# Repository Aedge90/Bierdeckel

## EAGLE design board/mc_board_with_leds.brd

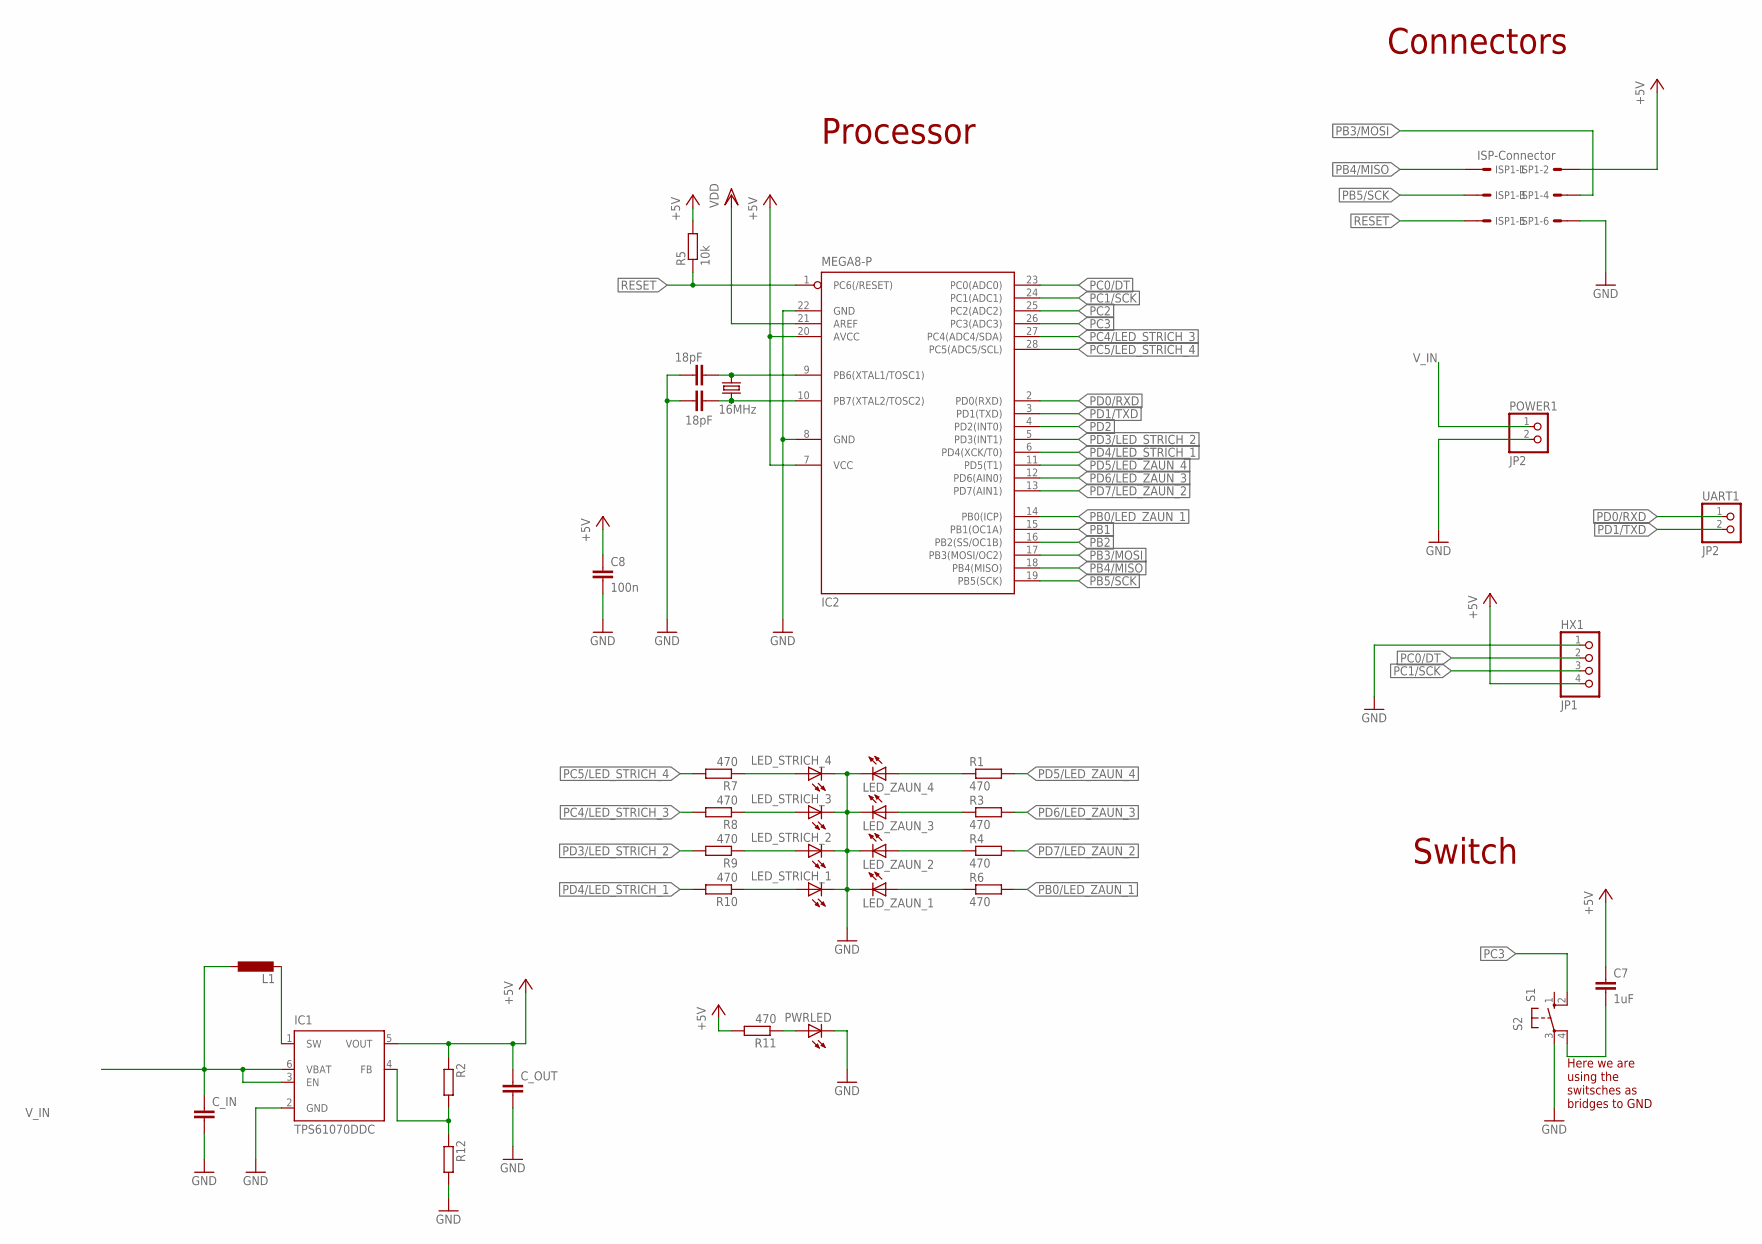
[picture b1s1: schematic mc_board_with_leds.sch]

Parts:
C5, C6: 18pF; C0805K
C7: 1uF; C0805
C8: 100n; C0805
C_IN: C-EUC0805; C0805
C_OUT: C-EUC0805; C0805
HX1: JP1; 1X04
IC1: TPS61070DDC; TSOT23-6_DDC
IC2: MEGA8-P; DIL28-3
ISP1: ISP-Connector; 057-006-1
L1: L-EUL4532P; L4532P
LED_STRICH_1, LED_STRICH_2, LED_STRICH_3, LED_STRICH_4: LED3MM
LED_ZAUN_1, LED_ZAUN_2, LED_ZAUN_3, LED_ZAUN_4: LED3MM
POWER1: JP2; 1X02
PWRLED: LED3MM
Q2: 16MHz; HC49/S
R1, R3, R4, R6, R7, R8, R9, R10, R11: 470; R0805
R2, R12: R-EU_R0805; R0805
R5: 10k; R1206
S2: S1; B3F-10XX
UART1: JP2; 1X02

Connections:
+5V: C7.1, C8.1, C_OUT.1, HX1.4, IC1.5 (VOUT), IC2.7 (VCC), IC2.20 (AVCC), ISP1.2, R2.1, R5.2, R11.2; also elsewhere on the board
GND: C5.2, C6.2, C8.2, C_IN.2, C_OUT.2, HX1.1, IC1.2 (GND), IC2.8 (GND), IC2.22 (GND), ISP1.6, LED_STRICH_1.K (C), LED_STRICH_2.K (C), LED_STRICH_3.K (C), LED_STRICH_4.K (C), LED_ZAUN_1.K (C), LED_ZAUN_2.K (C), LED_ZAUN_3.K (C), LED_ZAUN_4.K (C), POWER1.2, PWRLED.K (C), R12.2, S2.3; also elsewhere on the board
unnamed: LED_ZAUN_4.A, R1.1
unnamed: LED_ZAUN_3.A, R3.1
unnamed: LED_ZAUN_2.A, R4.1
unnamed: C5.1, IC2.10 (PB7(XTAL2/TOSC2)), Q2.2
unnamed 6: IC1.1 (SW), L1.2; also elsewhere on the board
unnamed: LED_ZAUN_1.A, R6.1
unnamed: LED_STRICH_4.A, R7.1
unnamed: LED_STRICH_3.A, R8.1
unnamed: LED_STRICH_2.A, R9.1
unnamed: LED_STRICH_1.A, R10.1
unnamed: PWRLED.A, R11.1
unnamed: C6.1, IC2.9 (PB6(XTAL1/TOSC1)), Q2.1
unnamed: C7.2, S2.4 (P1)
unnamed: IC1.4 (FB), R2.2, R12.1
PB0/LED_ZAUN_1: IC2.14 (PB0(ICP)), R6.2
PB1: IC2.15 (PB1(OC1A))
PB2: IC2.16 (PB2(SS/OC1B))
PB3/MOSI: IC2.17 (PB3(MOSI/OC2)), ISP1.4
PB4/MISO: IC2.18 (PB4(MISO)), ISP1.1
PB5/SCK: IC2.19 (PB5(SCK)), ISP1.3
PC0/DT: HX1.2, IC2.23 (PC0(ADC0))
PC1/SCK: HX1.3, IC2.24 (PC1(ADC1))
PC2: IC2.25 (PC2(ADC2))
PC3: IC2.26 (PC3(ADC3)), S2.2 (S1)
PC4/LED_STRICH_3: IC2.27 (PC4(ADC4/SDA)), R8.2
PC5/LED_STRICH_4: IC2.28 (PC5(ADC5/SCL)), R7.2
PD0/RXD: IC2.2 (PD0(RXD)), UART1.1
PD1/TXD: IC2.3 (PD1(TXD)), UART1.2
PD2: IC2.4 (PD2(INT0))
PD3/LED_STRICH_2: IC2.5 (PD3(INT1)), R9.2
PD4/LED_STRICH_1: IC2.6 (PD4(XCK/T0)), R10.2
PD5/LED_ZAUN_4: IC2.11 (PD5(T1)), R1.2
PD6/LED_ZAUN_3: IC2.12 (PD6(AIN0)), R3.2
PD7/LED_ZAUN_2: IC2.13 (PD7(AIN1)), R4.2
RESET: IC2.1 (PC6(/RESET)), ISP1.5, R5.1
VDD: IC2.21 (AREF)
V_IN: C_IN.1, IC1.3 (EN), IC1.6 (VBAT), L1.1, POWER1.1; also elsewhere on the board

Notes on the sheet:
Connectors
Switch
Processor
Here we are using the switsches as bridges to GND

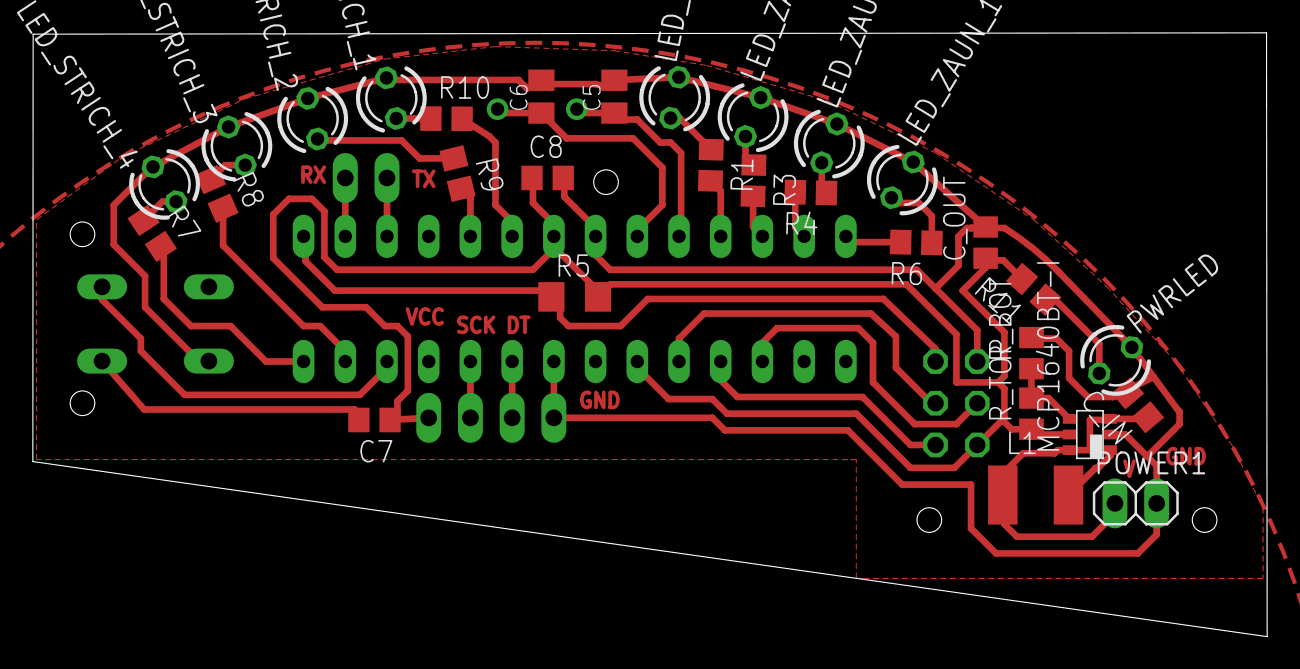
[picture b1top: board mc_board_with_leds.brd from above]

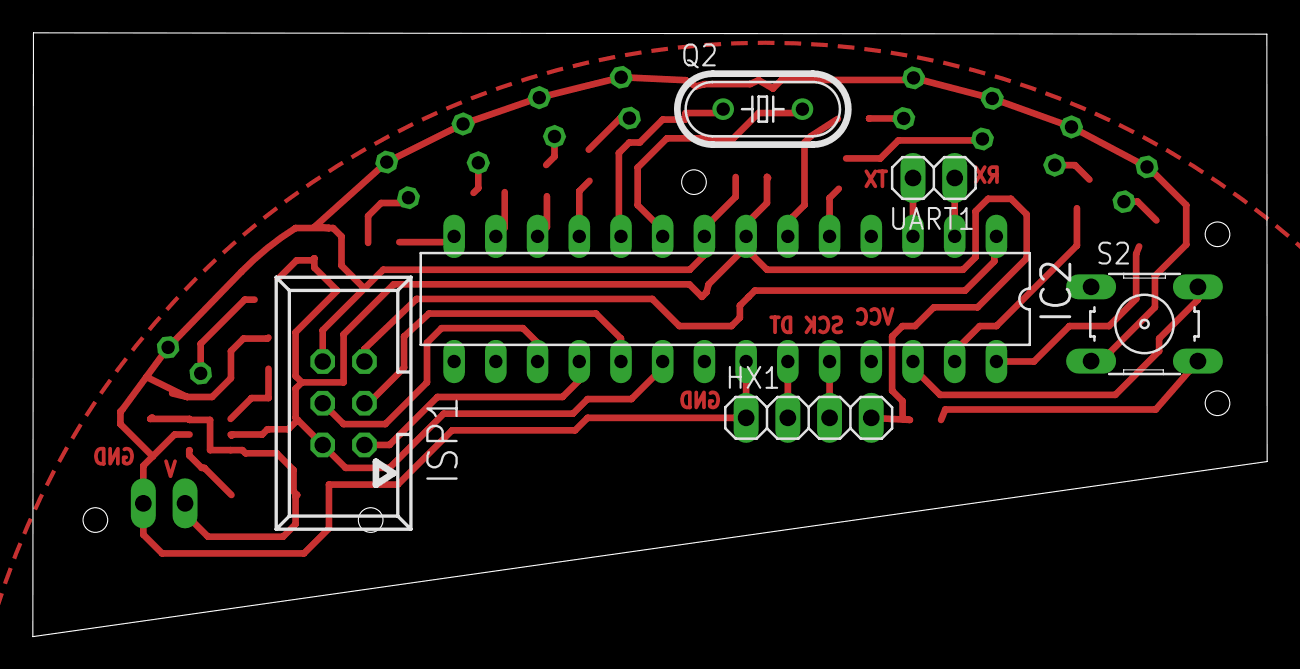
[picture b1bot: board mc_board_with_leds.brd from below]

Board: 2 copper layers, 75.2 x 36.8 mm, 36 parts (6 on the bottom side), 34 nets.

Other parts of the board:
MCP1640BT-I: TPS61070DDC; TSOT23-6_DDC
R_BOT: 330k; R0805
R_TOP: 560k; R0805

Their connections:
+5V: MCP1640BT-I.5, R_TOP.1; also elsewhere on the board
GND: MCP1640BT-I.2, R_BOT.2; also elsewhere on the board
unnamed 6: MCP1640BT-I.1; also elsewhere on the board
unnamed: MCP1640BT-I.4, R_BOT.1, R_TOP.2
V_IN: MCP1640BT-I.3, MCP1640BT-I.6; also elsewhere on the board

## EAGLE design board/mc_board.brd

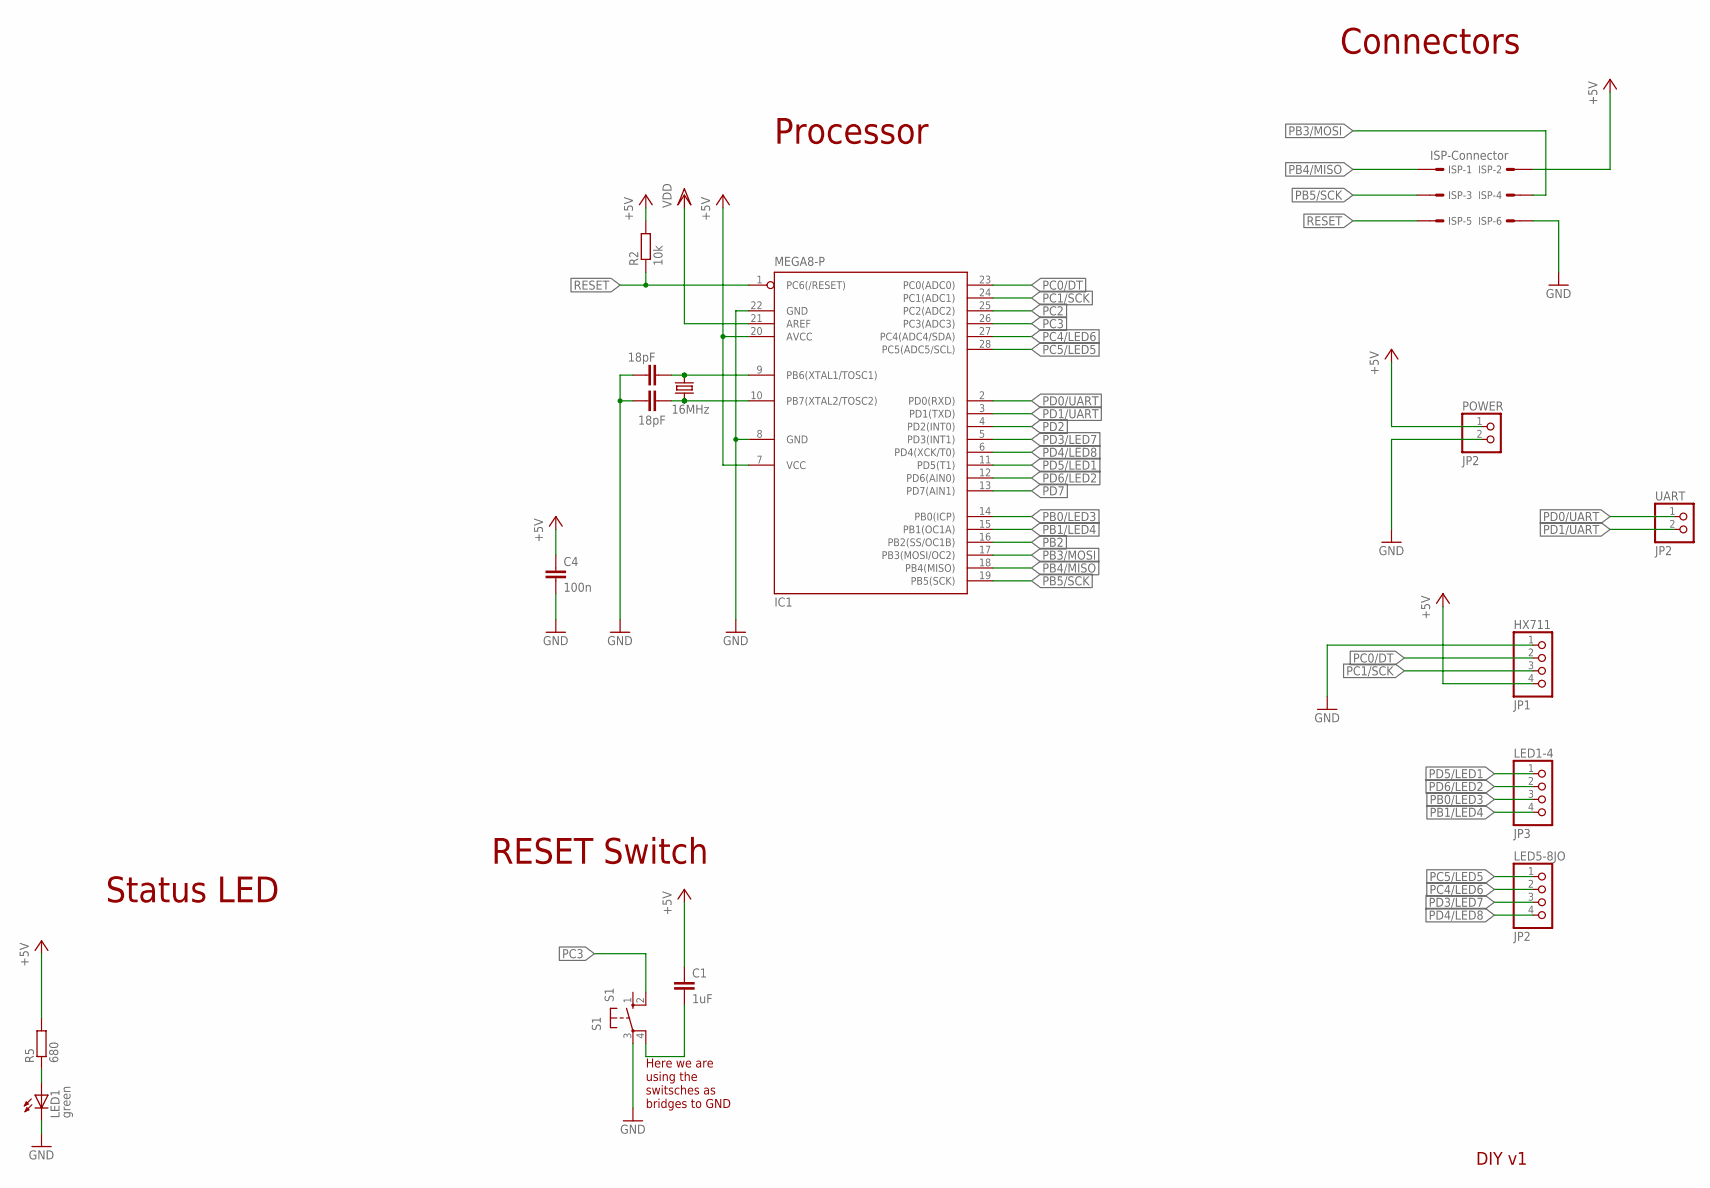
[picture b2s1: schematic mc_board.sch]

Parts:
C1: 1uF; C0805
C2, C3: 18pF; C0805K
C4: 100n; C0805
HX711: JP1; 1X04
IC1: MEGA8-P; DIL28-3
ISP: ISP-Connector; 057-006-1
LED1: green; CHIPLED_0805
LED1-4: JP3; 1X04
LED5-8JO: JP2; 1X04
POWER: JP2; 1X02
Q1: 16MHz; HC49/S
R2: 10k; R1206
R5: 680; R0805
S1: S1; B3F-10XX
UART: JP2; 1X02

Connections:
+5V: C1.1, C4.1, HX711.4, IC1.7 (VCC), IC1.20 (AVCC), ISP.2, POWER.1, R2.2, R5.2
GND: C2.2, C3.2, C4.2, HX711.1, IC1.8 (GND), IC1.22 (GND), ISP.6, LED1.C, POWER.2, S1.3
unnamed: LED1.A, R5.1
unnamed: C3.1, IC1.9 (PB6(XTAL1/TOSC1)), Q1.1
unnamed: C2.1, IC1.10 (PB7(XTAL2/TOSC2)), Q1.2
unnamed: C1.2, S1.4 (P1)
PB0/LED3: IC1.14 (PB0(ICP)), LED1-4.3
PB1/LED4: IC1.15 (PB1(OC1A)), LED1-4.4
PB2: IC1.16 (PB2(SS/OC1B))
PB3/MOSI: IC1.17 (PB3(MOSI/OC2)), ISP.4
PB4/MISO: IC1.18 (PB4(MISO)), ISP.1
PB5/SCK: IC1.19 (PB5(SCK)), ISP.3
PC0/DT: HX711.2, IC1.23 (PC0(ADC0))
PC1/SCK: HX711.3, IC1.24 (PC1(ADC1))
PC2: IC1.25 (PC2(ADC2))
PC3: IC1.26 (PC3(ADC3)), S1.2 (S1)
PC4/LED6: IC1.27 (PC4(ADC4/SDA)), LED5-8JO.2
PC5/LED5: IC1.28 (PC5(ADC5/SCL)), LED5-8JO.1
PD0/UART: IC1.2 (PD0(RXD)), UART.1
PD1/UART: IC1.3 (PD1(TXD)), UART.2
PD2: IC1.4 (PD2(INT0))
PD3/LED7: IC1.5 (PD3(INT1)), LED5-8JO.3
PD4/LED8: IC1.6 (PD4(XCK/T0)), LED5-8JO.4
PD5/LED1: IC1.11 (PD5(T1)), LED1-4.1
PD6/LED2: IC1.12 (PD6(AIN0)), LED1-4.2
PD7: IC1.13 (PD7(AIN1))
RESET: IC1.1 (PC6(/RESET)), ISP.5, R2.1
VDD: IC1.21 (AREF)

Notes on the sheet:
Status LED
Connectors
RESET Switch
DIY v1
Processor
Here we are using the switsches as bridges to GND

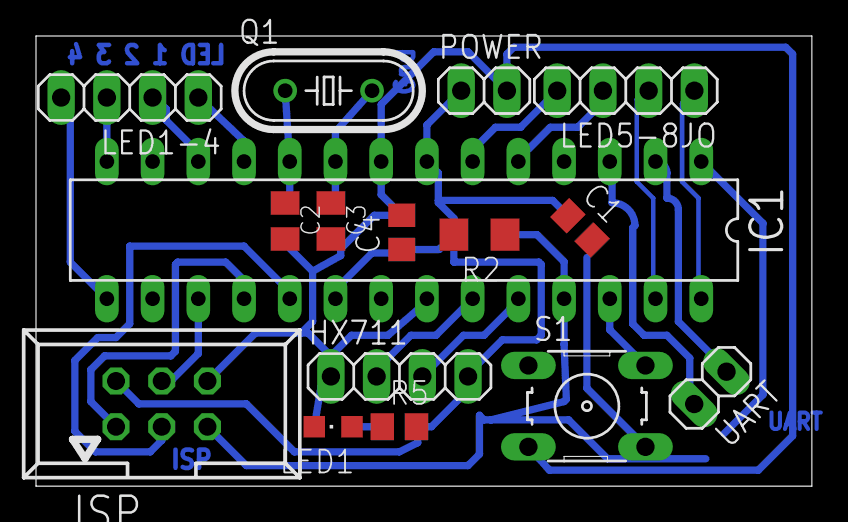
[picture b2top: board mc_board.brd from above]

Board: 2 copper layers, 43.1 x 25.0 mm, 16 parts (0 on the bottom side), 23 nets.

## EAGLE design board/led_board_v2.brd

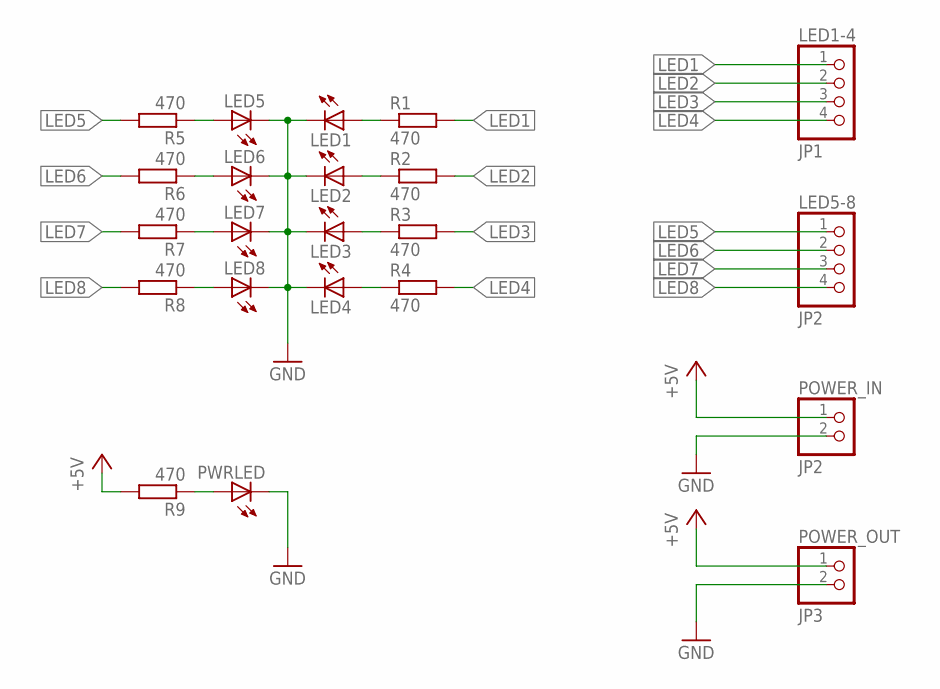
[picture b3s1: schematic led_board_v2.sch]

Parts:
LED1, LED2, LED3, LED4, LED5, LED6, LED7, LED8: LED3MM
LED1-4: JP1; 1X04
LED5-8: JP2; 1X04
POWER_IN: JP2; 1X02
POWER_OUT: JP3; 1X02
PWRLED: LED3MM
R1, R2, R3, R4, R5, R6, R7, R8, R9: 470; R0805

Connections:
+5V: POWER_IN.1, POWER_OUT.1, R9.2
GND: LED1.K (C), LED2.K (C), LED3.K (C), LED4.K (C), LED5.K (C), LED6.K (C), LED7.K (C), LED8.K (C), POWER_IN.2, POWER_OUT.2, PWRLED.K (C)
LED1: LED1-4.1, R1.2
LED2: LED1-4.2, R2.2
LED3: LED1-4.3, R3.2
LED4: LED1-4.4, R4.2
LED5: LED5-8.1, R5.2
LED6: LED5-8.2, R6.2
LED7: LED5-8.3, R7.2
LED8: LED5-8.4, R8.2
unnamed: LED1.A, R1.1
unnamed: LED2.A, R2.1
unnamed: LED3.A, R3.1
unnamed: LED4.A, R4.1
unnamed: LED5.A, R5.1
unnamed: LED6.A, R6.1
unnamed: LED7.A, R7.1
unnamed: LED8.A, R8.1
unnamed: PWRLED.A, R9.1

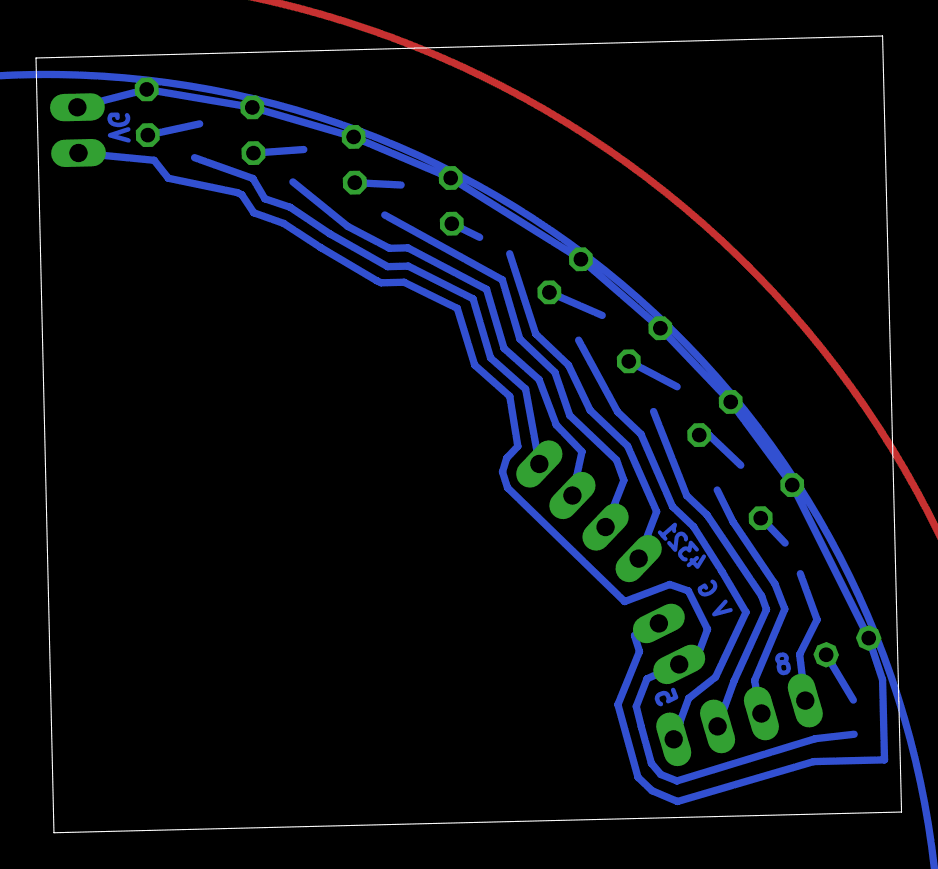
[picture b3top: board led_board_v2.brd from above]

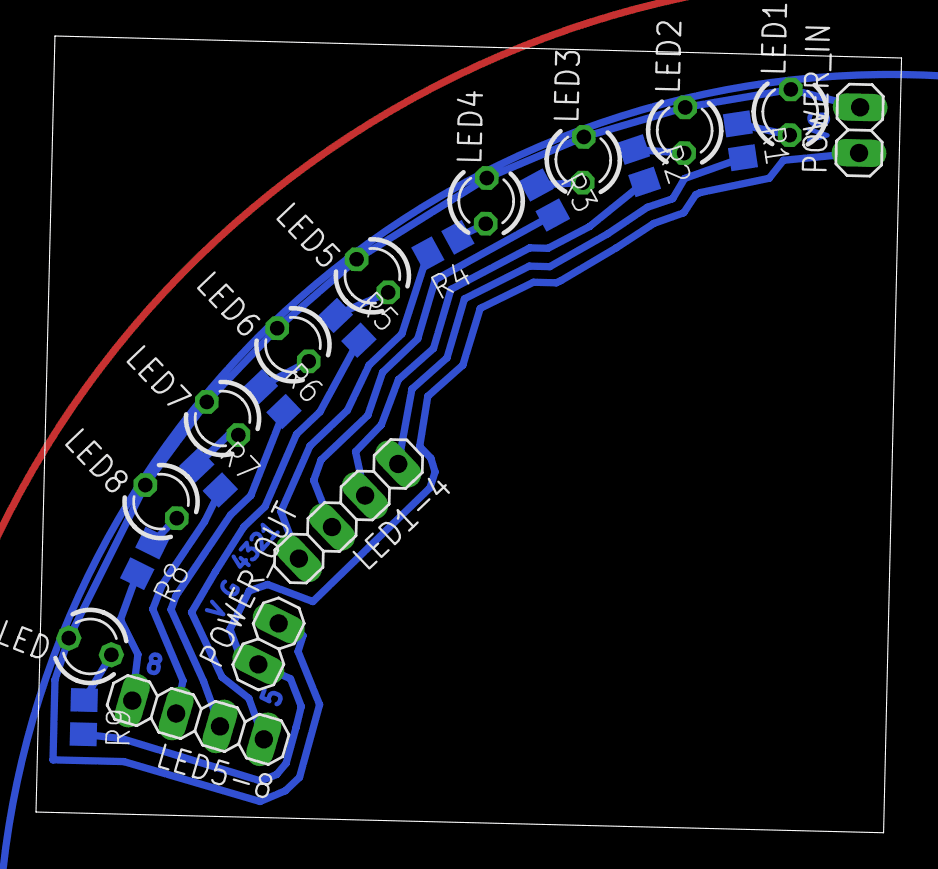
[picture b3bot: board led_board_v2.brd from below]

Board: 2 copper layers, 48.1 x 44.3 mm, 22 parts (22 on the bottom side), 19 nets.

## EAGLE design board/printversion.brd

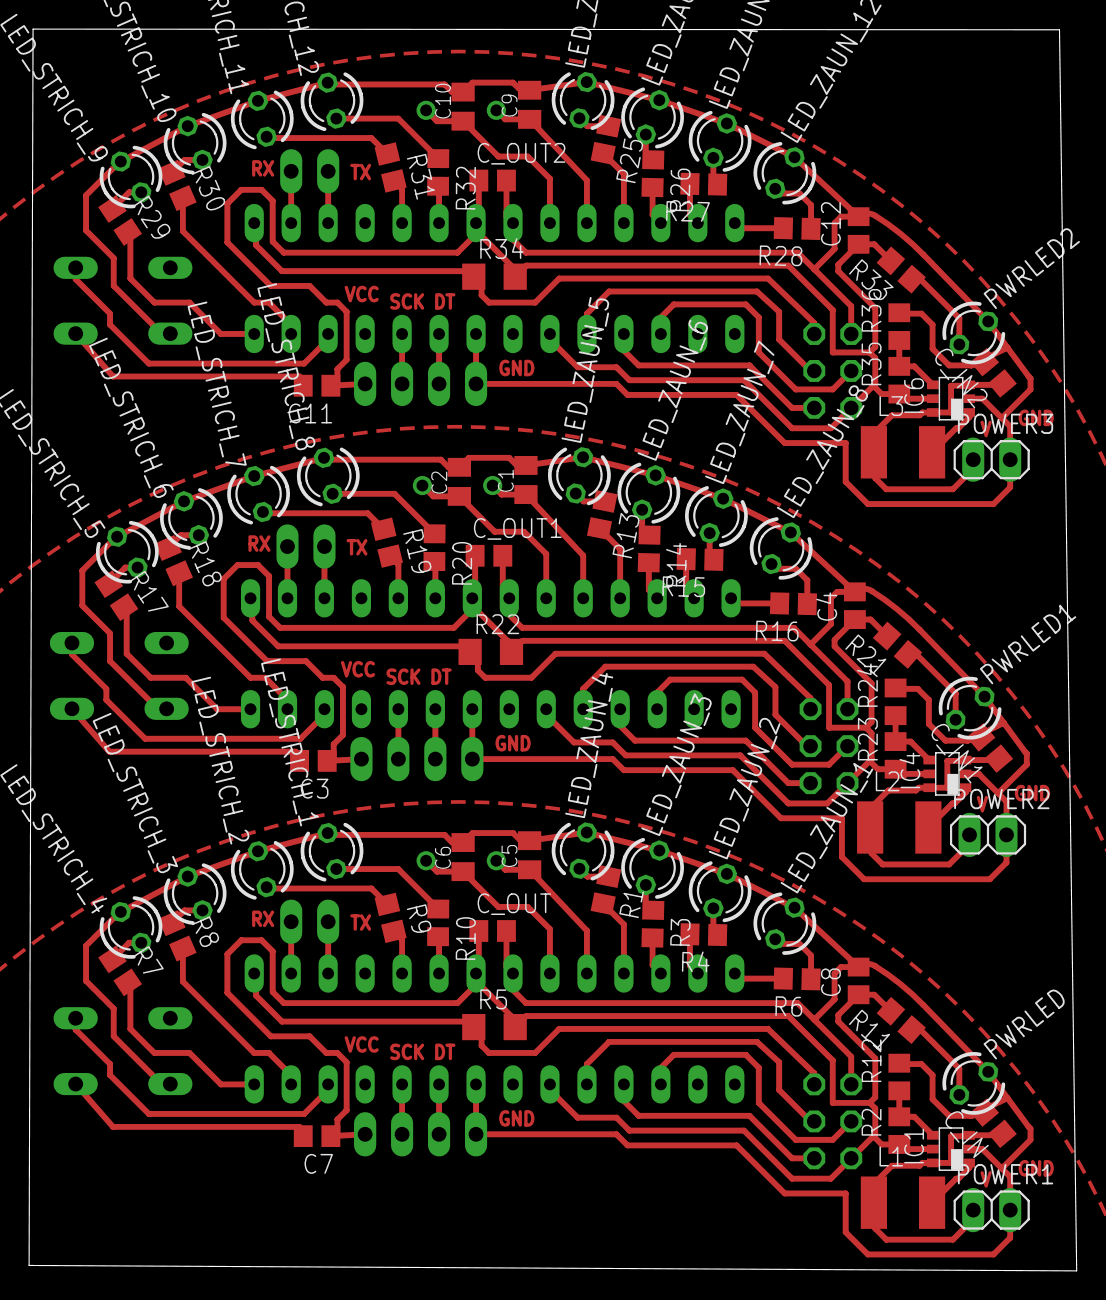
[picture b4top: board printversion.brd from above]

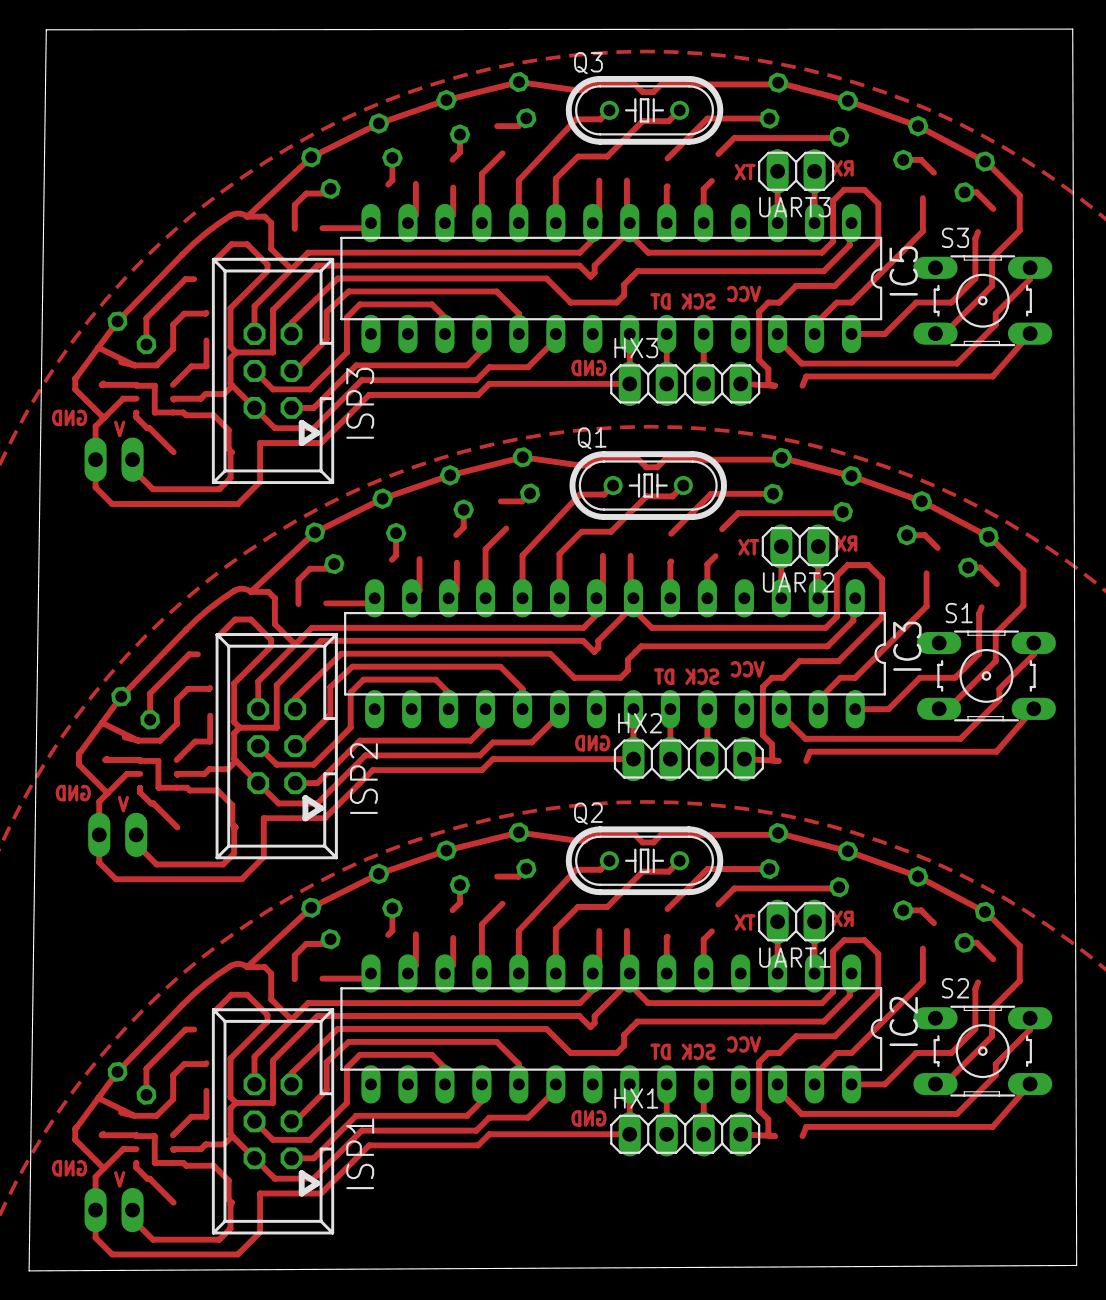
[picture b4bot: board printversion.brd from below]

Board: 2 copper layers, 72.0 x 85.3 mm, 108 parts (18 on the bottom side), 102 nets.

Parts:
C1, C2, C5, C6, C9, C10: 18pF; C0805K
C3, C7, C11: 1uF; C0805
C4, C8, C12: 100n; C0805
C_IN, C_IN1, C_IN2: C0805
C_OUT, C_OUT1, C_OUT2: C0805
HX1, HX2, HX3: JP1; 1X04
IC1, IC4, IC6: TPS61070DDC; TSOT23-6_DDC
IC2, IC3, IC5: MEGA8-P; DIL28-3
ISP1, ISP2, ISP3: ISP-Connector; 057-006-1
L1, L2, L3: L4532P
LED_STRICH_1, LED_STRICH_2, LED_STRICH_3, LED_STRICH_4, LED_STRICH_5, LED_STRICH_6, LED_STRICH_7, LED_STRICH_8, LED_STRICH_9, LED_STRICH_10, LED_STRICH_11, LED_STRICH_12: LED3MM
LED_ZAUN_1, LED_ZAUN_2, LED_ZAUN_3, LED_ZAUN_4, LED_ZAUN_5, LED_ZAUN_6, LED_ZAUN_7, LED_ZAUN_8, LED_ZAUN_9, LED_ZAUN_10, LED_ZAUN_11, LED_ZAUN_12: LED3MM
POWER1, POWER2, POWER3: JP2; 1X02
PWRLED, PWRLED1, PWRLED2: LED3MM
Q1, Q2, Q3: 16MHz; HC49/S
R1, R3, R4, R6, R7, R8, R9, R10, R11, R13, R14, R15, R16, R17, R18, R19, R20, R21, R25, R26, R27, R28, R29, R30, R31, R32, R33: 470; R0805
R2, R12, R23, R24, R35, R36: R0805
R5, R22, R34: 10k; R1206
S1, S2, S3: S1; B3F-10XX
UART1, UART2, UART3: JP2; 1X02

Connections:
+5V: C7.1, C8.1, C_OUT.1, HX1.4, IC1.5, IC2.7, IC2.20, ISP1.2, R2.1, R5.2, R11.2
+5V1: C3.1, C4.1, C_OUT1.1, HX2.4, IC3.7, IC3.20, IC4.5, ISP2.2, R21.2, R22.2, R23.1
+5V2: C11.1, C12.1, C_OUT2.1, HX3.4, IC5.7, IC5.20, IC6.5, ISP3.2, R33.2, R34.2, R35.1
GND: C5.2, C6.2, C8.2, C_IN.2, C_OUT.2, HX1.1, IC1.2, IC2.8, IC2.22, ISP1.6, LED_STRICH_1.K, LED_STRICH_2.K, LED_STRICH_3.K, LED_STRICH_4.K, LED_ZAUN_1.K, LED_ZAUN_2.K, LED_ZAUN_3.K, LED_ZAUN_4.K, POWER1.2, PWRLED.K, R12.2, S2.3
GND1: C1.2, C2.2, C4.2, C_IN1.2, C_OUT1.2, HX2.1, IC3.8, IC3.22, IC4.2, ISP2.6, LED_STRICH_5.K, LED_STRICH_6.K, LED_STRICH_7.K, LED_STRICH_8.K, LED_ZAUN_5.K, LED_ZAUN_6.K, LED_ZAUN_7.K, LED_ZAUN_8.K, POWER2.2, PWRLED1.K, R24.2, S1.3
GND2: C9.2, C10.2, C12.2, C_IN2.2, C_OUT2.2, HX3.1, IC5.8, IC5.22, IC6.2, ISP3.6, LED_STRICH_9.K, LED_STRICH_10.K, LED_STRICH_11.K, LED_STRICH_12.K, LED_ZAUN_9.K, LED_ZAUN_10.K, LED_ZAUN_11.K, LED_ZAUN_12.K, POWER3.2, PWRLED2.K, R36.2, S3.3
unnamed: LED_ZAUN_4.A, R1.1
unnamed: LED_ZAUN_3.A, R3.1
unnamed: LED_ZAUN_2.A, R4.1
unnamed: C5.1, IC2.10, Q2.2
unnamed: IC1.1, L1.2
unnamed: IC1.4, R2.2, R12.1
unnamed: LED_ZAUN_1.A, R6.1
unnamed: LED_STRICH_4.A, R7.1
unnamed: LED_STRICH_3.A, R8.1
unnamed: LED_STRICH_2.A, R9.1
unnamed: LED_STRICH_1.A, R10.1
unnamed: PWRLED.A, R11.1
unnamed: C6.1, IC2.9, Q2.1
unnamed: C7.2, S2.4
unnamed: LED_ZAUN_5.A, R13.1
unnamed: LED_ZAUN_6.A, R14.1
unnamed: LED_ZAUN_7.A, R15.1
unnamed: LED_ZAUN_8.A, R16.1
unnamed: LED_STRICH_5.A, R17.1
unnamed: LED_STRICH_6.A, R18.1
unnamed: LED_STRICH_7.A, R19.1
unnamed: LED_STRICH_8.A, R20.1
unnamed: PWRLED1.A, R21.1
unnamed: C1.1, IC3.10, Q1.2
unnamed: C2.1, IC3.9, Q1.1
unnamed: C3.2, S1.4
unnamed: IC4.1, L2.2
unnamed: IC4.4, R23.2, R24.1
unnamed: LED_ZAUN_9.A, R25.1
unnamed: LED_ZAUN_10.A, R26.1
unnamed: LED_ZAUN_11.A, R27.1
unnamed: LED_ZAUN_12.A, R28.1
unnamed: LED_STRICH_9.A, R29.1
unnamed: LED_STRICH_10.A, R30.1
unnamed: LED_STRICH_11.A, R31.1
unnamed: LED_STRICH_12.A, R32.1
unnamed: PWRLED2.A, R33.1
unnamed: C9.1, IC5.10, Q3.2
unnamed: C10.1, IC5.9, Q3.1
unnamed: C11.2, S3.4
unnamed: IC6.1, L3.2
unnamed: IC6.4, R35.2, R36.1
PB0/LED_ZAUN_1: IC2.14, R6.2
PB0/LED_ZAUN_2: IC3.14, R16.2
PB0/LED_ZAUN_3: IC5.14, R28.2
PB3/MOSI: IC2.17, ISP1.4
PB3/MOSI1: IC3.17, ISP2.4
PB3/MOSI2: IC5.17, ISP3.4
PB4/MISO: IC2.18, ISP1.1
PB4/MISO1: IC3.18, ISP2.1
PB4/MISO2: IC5.18, ISP3.1
PB5/SCK: IC2.19, ISP1.3
PB5/SCK1: IC3.19, ISP2.3
PB5/SCK2: IC5.19, ISP3.3
PC0/DT: HX1.2, IC2.23
PC0/DT1: HX2.2, IC3.23
PC0/DT2: HX3.2, IC5.23
PC1/SCK: HX1.3, IC2.24
PC1/SCK1: HX2.3, IC3.24
PC1/SCK2: HX3.3, IC5.24
PC3: IC2.26, S2.2
PC4: IC3.26, S1.2
PC4/LED_STRICH_1: IC3.27, R18.2
PC4/LED_STRICH_2: IC5.27, R30.2
PC4/LED_STRICH_3: IC2.27, R8.2
PC5/LED_STRICH_1: IC3.28, R17.2
PC5/LED_STRICH_2: IC5.28, R29.2
PC5/LED_STRICH_4: IC2.28, R7.2
PC6: IC5.26, S3.2
PD0/RXD: IC2.2, UART1.1
PD0/RXD1: IC3.2, UART2.1
PD0/RXD2: IC5.2, UART3.1
PD1/TXD: IC2.3, UART1.2
PD1/TXD1: IC3.3, UART2.2
PD1/TXD2: IC5.3, UART3.2
PD3/LED_STRICH_1: IC3.5, R19.2
PD3/LED_STRICH_2: IC2.5, R9.2
PD3/LED_STRICH_3: IC5.5, R31.2
PD4/LED_STRICH_1: IC2.6, R10.2
PD4/LED_STRICH_2: IC3.6, R20.2
PD4/LED_STRICH_3: IC5.6, R32.2
PD5/LED_ZAUN_1: IC3.11, R13.2
PD5/LED_ZAUN_2: IC5.11, R25.2
PD5/LED_ZAUN_4: IC2.11, R1.2
PD6/LED_ZAUN_1: IC3.12, R14.2
PD6/LED_ZAUN_2: IC5.12, R26.2
PD6/LED_ZAUN_3: IC2.12, R3.2
PD7/LED_ZAUN_1: IC3.13, R15.2
PD7/LED_ZAUN_2: IC2.13, R4.2
PD7/LED_ZAUN_3: IC5.13, R27.2
RESET: IC2.1, ISP1.5, R5.1
RESET1: IC3.1, ISP2.5, R22.1
RESET2: IC5.1, ISP3.5, R34.1
V_IN: C_IN.1, IC1.3, IC1.6, L1.1, POWER1.1
V_IN1: C_IN1.1, IC4.3, IC4.6, L2.1, POWER2.1
V_IN2: C_IN2.1, IC6.3, IC6.6, L3.1, POWER3.1

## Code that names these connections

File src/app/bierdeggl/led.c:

#include "led.h"
#include "timer.h"
#include <avr/io.h>


#define LEDZaun1 (1<<PB0)
#define LEDZaun2 (1<<PD7)
#define LEDZaun3 (1<<PD6)
#define LEDZaun4 (1<<PD5)
#define LEDStrich1 (1<<PD4)
#define LEDStrich2 (1<<PD3)
#define LEDStrich3 (1<<PC4)
#define LEDStrich4 (1<<PC5)

// defines the data direction of the pins. 1 is output, 0 is input
void led_init(void){
	DDRD |= 0b11111000;
	DDRC |= 0b00110000;
	DDRB |= 0b00000001;
}

void led_show(uint8_t n) {
	int zaun = n/5;
	int strich = n-(zaun*5);
	switch(zaun){
		case(4):
			PORTD |= LEDZaun4;
		case(3):
			PORTD |= LEDZaun3;
		case(2):
			PORTD |= LEDZaun2;
		case(1):
			PORTB |= LEDZaun1;
			break;
		default:
			PORTD &= ~(LEDZaun4 | LEDZaun3 | LEDZaun2);
			PORTB &= ~(LEDZaun1);
	}
	switch(strich){
		case(4):
			PORTC |= LEDStrich4;
		case(3):
			PORTC |= LEDStrich3;
		case(2):
			PORTD |= LEDStrich2;
		case(1):
			PORTD |= LEDStrich1;
			break;
		default:
			PORTC &= ~(LEDStrich4 | LEDStrich3);
			PORTD &= ~(LEDStrich2 | LEDStrich1);
	}
}

void led_blink(uint8_t n) {
	timer_wait(1);
	led_show(0);
	timer_wait(1);
	led_show(n);
}

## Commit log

2015-10-26 Initial Commit with presentation
2015-10-26 Initial commit with contributors
2015-10-26 First Version of Presentation
2015-10-28 Images 4 Extensions
    + centered images
2015-10-29 Erweiterungenfolie
2015-12-08 Initial design
2015-12-25 Removed Merge Conflict Files
2015-12-25 Readded previous removed Files
2015-12-25 Removed duplicate Files:
2016-01-28 Changed permissions due to move to ntfs part
2016-01-28 Added Bierdeggl Application (TinyUSBboard version)
2016-01-29 added led board and mc board layouts
2016-01-29 added basic documentation
2016-01-31 Renamed bierdeggl app folder
2016-01-31 Arduino Bierdeggl Application
    working!!
2016-02-01 Implemented Application with UART, without Arduino IDE
2016-02-01 added some comments
2016-02-01 Refactored LED
2016-02-02 Implemented sleep mode
2016-02-02 Extended Makefile for Arduino as ISP
    Bugfix in led.c: PC6/RST was LED Pin -> changed to PC4
2016-02-02 added UART pins to layout
2016-02-03 tweaked board layout, defined pins in led.c accordingly
2016-02-03 added values to resistors on led board
2016-02-03 Added some testing gimmicks +@s
2016-02-03 HX711: Changed return type of get_g to int32_t
2016-02-03 Working on a ntfs partition is a very bad idea...
2016-02-03 Added skeleton for final presentation
2016-02-03 n baar bildschn
2016-02-04 documentation with missing pictures
2016-02-04 Added source code to presentation
2016-02-04 Added prevention for false indication
2016-02-04 added images to documentation
2016-02-04 added complete board image
2016-02-04 Vortrag un so ....
2016-02-04 updated image
2016-02-05 doku almost done
2016-02-05 update refs to figures
2016-02-05 added more images
2016-02-05 F**k permissions on ntfs
2016-02-05 Format + Rechtschreibfehler...
2016-02-05 Kraut und Rüben
2016-02-05 blubb
2016-02-06 doku finished
2016-02-07 increased resolution of some images
2016-02-10 improved board layout
2016-02-10 even better board layout
2016-02-11 new idea for led board layout
2016-02-11 fixed led board layout v2
2016-02-11 removed gnd pin form board
2016-02-11 changed reset button to normal button
2016-02-11 started to swap layer to bottom. not done!
2016-02-18 added new version of case
2016-02-18 fixed non manifold error
2016-02-18 added padding
2016-02-19 added filler
2016-02-19 added colors and Bounding Boxes
2016-02-19 added last Bounding Box
2016-02-19 fixed something and reordered code
2016-02-19 fixed BoardBB and tweaked layout
2016-02-22 added leds to board
2016-02-22 fixed bug and updated BoardBB
2016-02-22 added new board version with leds
2016-02-22 board finished
2016-02-22 changed code to match pin layout
2016-02-22 renamed LEDs in .c file and schematic
2016-02-22 reordered leds
2016-02-22 increased thickness
2016-02-23 leds now seperate
2016-02-23 modeled an led
2016-02-23 fixed problems with Fill()
2016-02-23 fixed led hole height
2016-02-23 fixed coloring
2016-02-23 better led model
2016-02-24 small changes
2016-02-24 added step up converter to schematic
2016-02-25 led board and case now match exactly
2016-02-25 integrated pull up into board layout
2016-02-26 added names to board
2016-02-26 changed names and corrected pin assignment of hx711
2016-02-26 added drill holes
2016-02-26 added ground fill
2016-02-26 fixed it
2016-02-26 printable version
2016-02-28 added printversion with multiple boards per page
2016-03-12 all standard layer now visible again
2016-04-16 replaced some things on the board
2016-04-16 added missing values
2016-04-16 renamed LEDs properly
2018-04-20 added pdf
2018-04-20 added test makefile to set correct fuse bits. Still not working yet
2018-05-05 added working line to makefile, which works for test project
2018-05-05 added the test code
2018-05-05 removed unused versions of the code
2018-05-05 fixed makefile and fixed wrong code
2018-05-05 fixed LED not turning off
2018-05-05 fixed wrong counting in test
2018-05-06 fixed fuse bits in makefile and added image which describes the used fuse bits
2018-05-06 fixed Makefile again to work with newest avrdude version, where undefined bits are read as 1 in the verification step
2018-05-06 added comments + removed unnecessary code
2018-05-06 added comments
2018-05-06 timer_wait now actually waits the specified amount of seconds
2018-05-27 added README
2018-05-27 removed unnecessary files
2018-06-02 removed duplicate variable definitions
2018-07-01 fixed timer interfering with UART

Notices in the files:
parts and their libraries:
SparkFun: Licensing: CC v3.0 Share-Alike You are welcome to use this library for commercial purposes.
